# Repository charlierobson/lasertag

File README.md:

# lasertag

### What
Simple laser-tag style game implementation using hacked Namco G-con and Arduino/ESP32.

### Why
Why not.

### How

#### Shot detection
TSOP38238 style IR receiver is attached to external interrupt pin. On change interrupt detects a falling or rising edge produced by the module's output pin. The signal is active low, and pulls its output to ground when a 38khz modulated signal is being detected. On falling edge timer 1 is reset to 0 where it counts up. Roughly speaking on deteting a rising edge timer 1's value is interpreted as a 1 or 0 and shifted into an accumulator. When 16 bits have been received the value is parity achecked and if it appears good then it is stashed in a circular buffer. Because this happens in an interrupt we never miss a hit.

The buffer is checked every game loop and if it contains any tags then the received data is evaluated. The bit fields of the command word are as follows:

| 16-10 | 9-1 | 0 |
|----|--------|-----|---|
| command code | command data | parity check bit |

Parity is even. Bits are encoded similarly to 'miles tag' standard. Multiples of 600us pulses are transmitted by the tagger. The length of a pulse denotes its value. 4x600us for the start bit, 2x600us for a '1' bit and 1x600us for a '0' bit. Signal is RTZ, with a 600us high period separating the bits.

For example. At the reciver's output pin we see a signal like:

```
... ++++++++++----+--+-+--+--+-+--+--+-+-+-+-+-+-+--+-+--+--++++++ ...
                 S  1 0  1  1 0  1  1 0 0 0 0 0 0  1 0  1  1
```

Where '+' = high period of 600us, '-' = low period of 600us. This therefore represents reception of the folowing code:

Command code: 101101
Command data: 1000000101
Parity: 1

#### Shot transmission

Generation of 38khz signal is handed off to hardware. On AVR timer 2 is used to toggle an output pin on hardware timer value match producing a 50% PWM signal at the pin. The PWM runs continuously and is modulated by setting the direction of the output pin. When direction is OUT then the signal is output to the IR LED. When it's IN the LED is off. 

---

### Useful shiz

[Timer-free tone library](https://bitbucket.org/teckel12/arduino-timer-free-tone/wiki/Home#!example)

[Soft-latching switches](https://www.youtube.com/watch?v=7D9L9oS4AJM)

[Audio using DDS](https://hackaday.com/2016/02/12/embed-with-elliot-audio-playback-with-direct-digital-synthesis/)

[38khz pwm using timer hardware](https://forum.arduino.cc/index.php?topic=102430.msg773556#msg773556)

[WS28x LEDS aren't so picky, really](https://wp.josh.com/2014/05/13/ws2812-neopixels-are-not-so-finicky-once-you-get-to-know-them/), [WS2812 code](https://github.com/bigjosh/SimpleNeoPixelDemo)

[Lense thoughts 1](http://webcache.googleusercontent.com/search?q=cache:d14Z821idtkJ:www.lasertagparts.com/mtoptics.htm+&cd=1&hl=en&ct=clnk&gl=uk), [2](http://webcache.googleusercontent.com/search?q=cache:e1SMQ_9_ErMJ:alumnus.caltech.edu/~leif/infratag/lens_choice.html+&cd=3&hl=en&ct=clnk&gl=uk)

[DIY gun guide](http://www.lasertag.co.uk/PDF_files/sgconst.pdf)

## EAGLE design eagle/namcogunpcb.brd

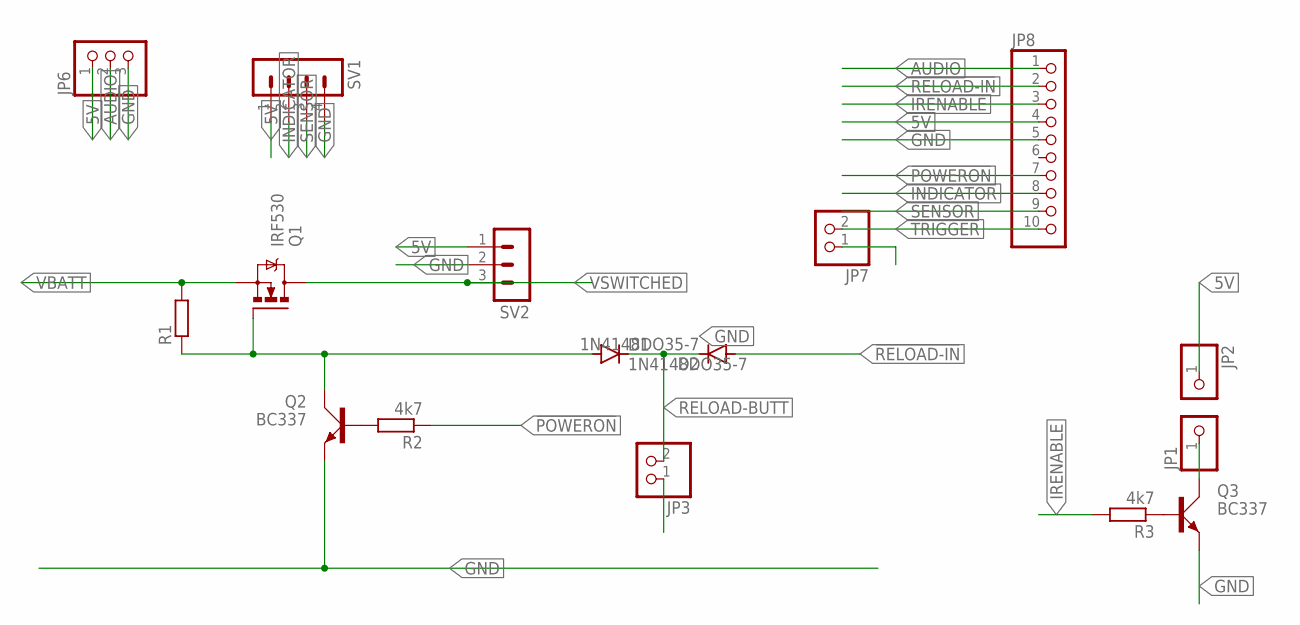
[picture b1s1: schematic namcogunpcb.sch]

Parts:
D1, D2: 1N4148DO35-7; DO35-7
JP1, JP2: PINHD-1X1; 1X01
JP3, JP7: PINHD-1X2; 1X02
JP6: PINHD-1X3; 1X03
JP8: PINHD-1X10; 1X10
Q1: IRF530; TO220BV
Q2, Q3: BC337; SOT54A
R1: R-EU_0207/10; 0207/10
R2, R3: 4k7; 0207/10
SV1: MA04-1
SV2: MA03-1

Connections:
5V: JP2.1, JP6.1, JP8.4, SV1.1, SV2.1
!POWERON: JP8.7, R2.1
!RELOAD-IN: D2.A, JP8.2
!TRIGGER: JP7.2, JP8.10
AUDIO: JP6.2, JP8.1
GND: JP3.1, JP6.3, JP7.1, JP8.5, Q2.E, Q3.E, SV1.4, SV2.2
INDICATOR: JP8.8, SV1.2
IRENABLE: JP8.3, R3.2
unnamed: JP1.1, Q3.C
unnamed: D1.A, Q1.G, Q2.C, R1.1
unnamed: Q3.B, R3.1
unnamed: Q2.B, R2.2
RELOAD-BUTT: D1.C, D2.C, JP3.2
SENSOR: JP8.9, SV1.3
VBATT: Q1.S, R1.2
VSWITCHED: Q1.D, SV2.3

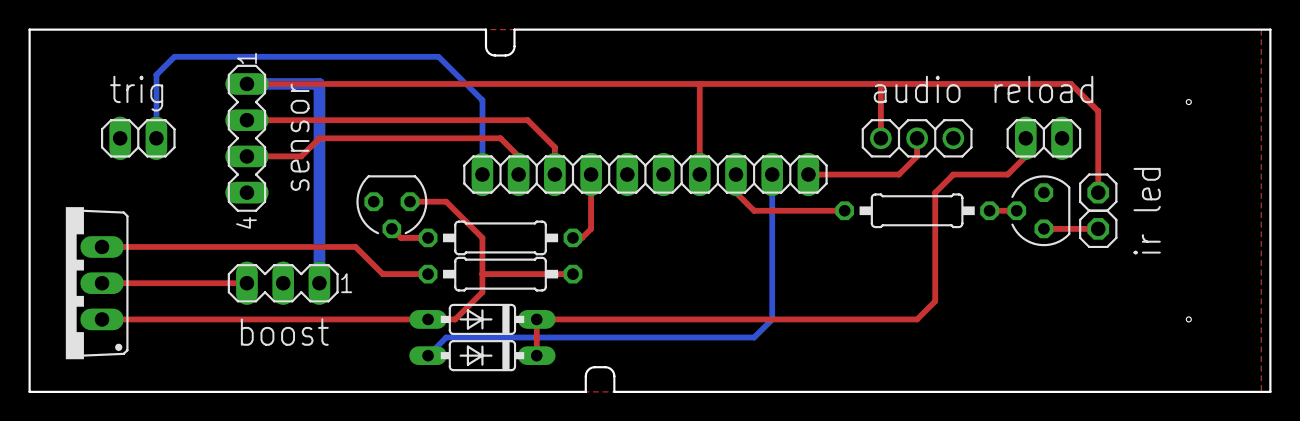
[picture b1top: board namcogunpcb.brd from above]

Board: 2 copper layers, 87.0 x 25.4 mm, 16 parts (0 on the bottom side), 16 nets.

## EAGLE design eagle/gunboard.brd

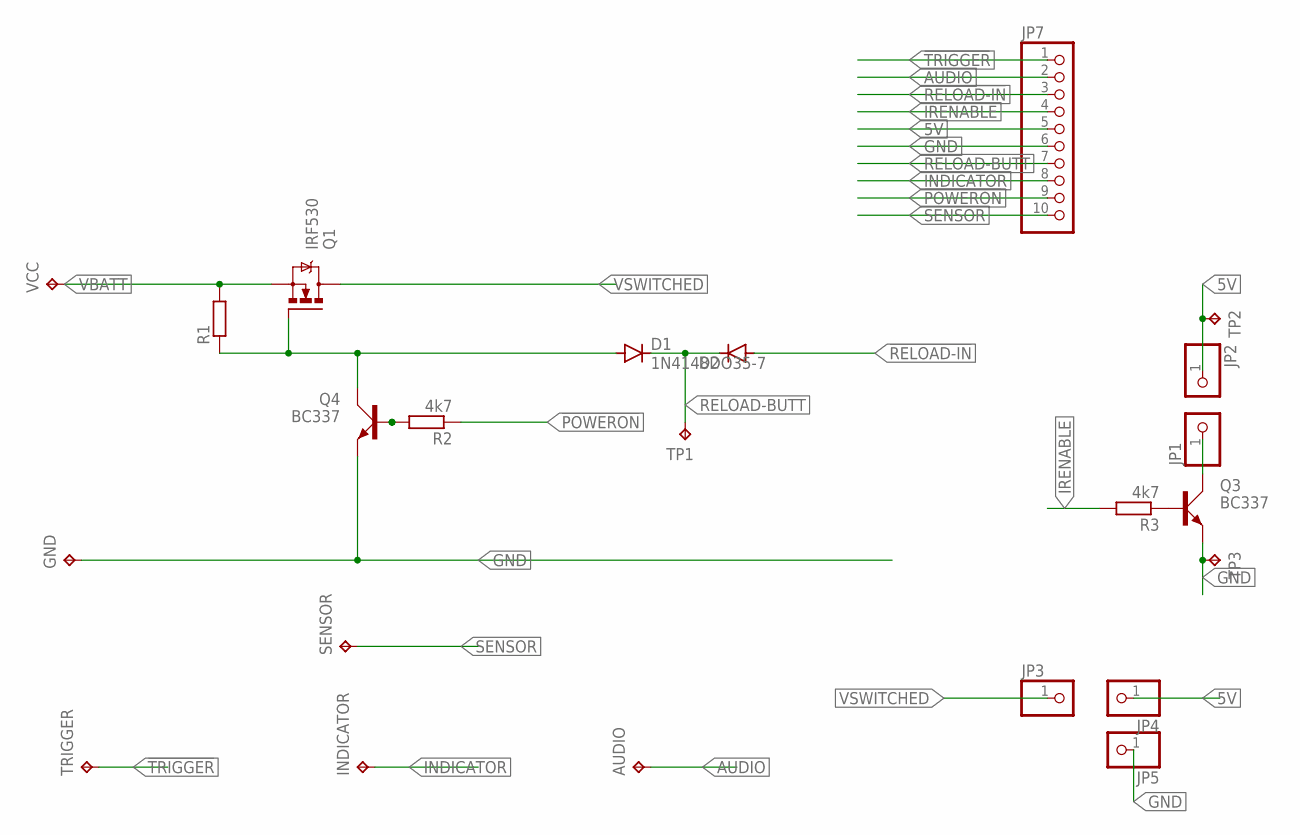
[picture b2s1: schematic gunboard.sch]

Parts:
AUDIO: TPTP20SQ; TP20SQ
D1: 1N4148DO35-7; DO35-7
D2: DIODE-DO35-10; DO35-10
GND: TPTP20SQ; TP20SQ
INDICATOR: TPTP20SQ; TP20SQ
JP1, JP2, JP3, JP4, JP5: PINHD-1X1; 1X01
JP7: PINHD-1X10; 1X10
Q1: IRF530; TO220BV
Q3, Q4: BC337; SOT54A
R1: R-EU_0207/5V; 0207/5V
R2, R3: 4k7; 0207/10
SENSOR: TPTP20SQ; TP20SQ
TP1, TP2, TP3: TPTP20SQ; TP20SQ
TRIGGER: TPTP20SQ; TP20SQ
VCC: TPTP20SQ; TP20SQ

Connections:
5V: JP2.1, JP4.1, JP7.5, TP2.TP
!POWERON: JP7.9, R2.1
!RELOAD-IN: D2.A, JP7.3
!TRIGGER: JP7.1, TRIGGER.TP
AUDIO: AUDIO.TP, JP7.2
GND: GND.TP, JP5.1, JP7.6, Q3.E, Q4.E, TP3.TP
INDICATOR: INDICATOR.TP, JP7.8
IRENABLE: JP7.4, R3.2
unnamed: JP1.1, Q3.C
unnamed: D1.A, Q1.G, Q4.C, R1.1
unnamed: Q3.B, R3.1
unnamed: Q4.B, R2.2
RELOAD-BUTT: D1.C, D2.C, JP7.7, TP1.TP
SENSOR: JP7.10, SENSOR.TP
VBATT: Q1.S, R1.2, VCC.TP
VSWITCHED: JP3.1, Q1.D

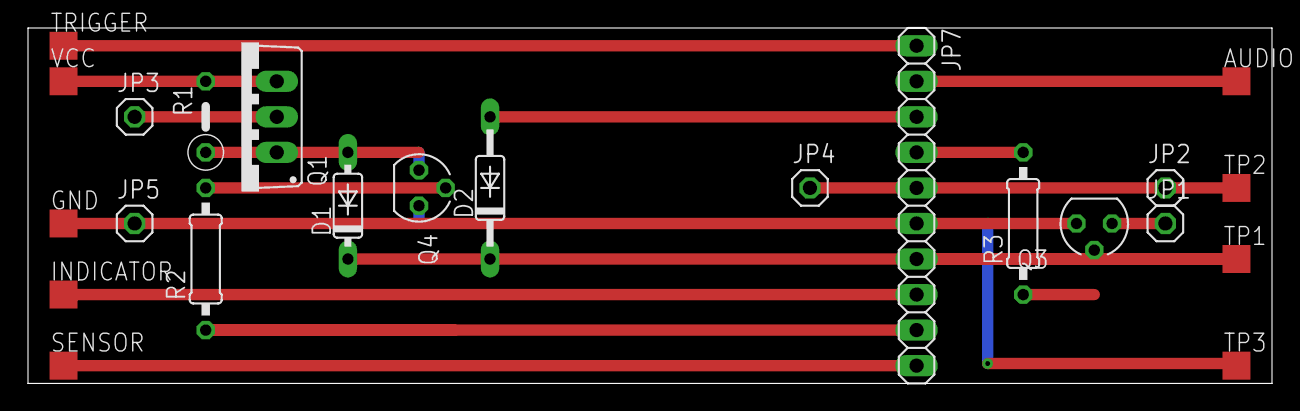
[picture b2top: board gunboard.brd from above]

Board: 2 copper layers, 88.9 x 25.4 mm, 23 parts (0 on the bottom side), 16 nets.

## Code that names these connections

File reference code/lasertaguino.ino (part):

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int triggerPin             = 3;      // Push button for primary fire. Low = pressed
int trigger2Pin            = 13;     // Push button for secondary fire. Low = pressed
int speakerPin             = 4;      // Direct output to piezo sounder/speaker
int audioPin               = 9;      // Audio Trigger. Can be used to set off sounds recorded in the kind of electronics you can get in greetings card that play a custom message.
int lifePin                = 6;      // An analogue output (PWM) level corresponds to remaining life. Use PWM pin: 3,5,6,9,10 or 11. Can be used to drive LED bar graphs. eg LM3914N
int ammoPin                = 5;      // An analogue output (PWM) level corresponds to remaining ammunition. Use PWM pin: 3,5,6,9,10 or 11.
int hitPin                 = 7;      // LED output pin used to indicate when the player has been hit.
int IRtransmitPin          = 2;      // Primary fire mode IR transmitter pin: Use pins 2,4,7,8,12 or 13. DO NOT USE PWM pins!! More info: http://j44industries.blogspot.com/2009/09/arduino-frequency-generation.html#more
int IRtransmit2Pin         = 8;      // Secondary fire mode IR transmitter pin:  Use pins 2,4,7,8,12 or 13. DO NOT USE PWM pins!!
int IRreceivePin           = 12;     // The pin that incoming IR signals are read from
//int IRreceive2Pin          = 11;     // Allows for checking external sensors are attached as well as distinguishing between sensor locations (eg spotting head shots)
// Minimum gun requirements: trigger, receiver, IR led, hit LED.

// Player and Game details
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// Code Variables
int timeOut                = 0;      // Deffined in frequencyCalculations (IRpulse + 50)
int FIRE                   = 0;      // 0 = don't fire, 1 = Primary Fire, 2 = Secondary Fire
int TR                     = 0;      // Trigger Reading
int LTR                    = 0;      // Last Trigger Reading
int T2R                    = 0;      // Trigger 2 Reading (For secondary fire)
int LT2R                   = 0;      // Last Trigger 2 Reading (For secondary fire)

// Signal Properties
int IRpulse                = 600;    // Basic pulse duration of 600uS MilesTag standard 4*IRpulse for header bit, 2*IRpulse for 1, 1*IRpulse for 0.
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void triggers() { // Checks to see if the triggers have been presses
  LTR = TR;       // Records previous state. Primary fire
  LT2R = T2R;     // Records previous state. Secondary fire
  TR = digitalRead(triggerPin);      // Looks up current trigger button state
  T2R = digitalRead(trigger2Pin);    // Looks up current trigger button state
  // Code looks for changes in trigger state to give it a semi automatic shooting behaviour
  if (TR != LTR && TR == LOW) {
    FIRE = 1;
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
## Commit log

2019-06-21 basic framework of gun receiver and game state
2019-06-21 subclass guns for player and referee
2019-06-21 adding older stuff
2019-06-21 add originl code in case
2019-06-21 command data stream builder
2019-06-21 comments
2019-06-21 receiving hits!
2019-07-20 led indicator of shot
2019-07-21 reconfigure receive code, arduino base is effectively a target now
2019-07-21 debounce trigger
2019-07-22 move toward single source/multi architecture
2019-07-22 now compiling for both avr and esp32
2019-07-23 echo add gitignore
2019-07-23 clean up
2019-08-08 add trigger class
2019-08-08 adding sfx class
2019-08-09 add shot audio
2019-08-09 phew - working again
2019-08-09 sfx!
2019-08-09 stripping dependencies from classes
2019-08-13 active low buttons d'oh
2019-08-13 update sfx
2019-08-13 fix audio data segment allocation
2019-08-13 add board
2019-08-13 power on triggers
2019-08-13 new pins
2019-08-13 ignore eagle lock files
2019-08-14 adding pcb as manufactured
2019-09-01 audio update, converter
2019-09-02 add ff nope
2019-09-02 change how triggers work
2019-09-03 add comment
2019-09-03 must release reload butts before powering off, reload on release
2019-09-03 reinstate justreleased state
2019-10-07 new sounds
2020-01-06 Update convert.sh
    using s8/pcm_s8 produces a much clearer sound

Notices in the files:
reference code/lasertaguino.ino:
Licence: Attribution Share Alike: Give credit where credit is due, but you can do what you like with the code.
